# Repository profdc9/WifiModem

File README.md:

# WiFi Modem

This is a simple layout for connection a ESP12E to a serial port so that a serial to wireless gateway can be used.  It connects RTS/CTS for flow control (when supported) and has DB9 female/male and DB25 female/male connectors.  The particular gender of the connector can be mounted on the side of the board indicated by the silkscreening.  DB25 male is used to connect directly to an Apple Super Serial Card.  DB25 female is the standard connection of old-style dialup modems.  There are jumpers that swap TXD/RXD, RTS/CTS, and DTR/DSR to implement a built-in null modem changer.

There are several types of firmware that could be used on it.

https://github.com/jeelabs/esp-link

ESP Link is a firmware that enables remote access to a microcontroller or serial port through a web page or TCP port.

https://github.com/dhansel/WifiModem

https://github.com/jsalin/esp8266_modem

https://github.com/maccasoft/WifiModem/blob/master/WifiModem.ino

https://github.com/ssshake/vintage-computer-wifi-modem

https://github.com/stardot/esp8266_modem/wiki

https://github.com/RolandJuno/esp8266_modem    (implements CTS)

https://github.com/bozimmerman/Zimodem

A firmware image "zimodem.ino.nodemcu-3.4.bin" may be downloaded from:

http://subethasoftware.com/files/zimodem/

For using with ZiModem, use the following settings:

```
ATS47=5
OK
ATS49=15
OK
ATS51=13
OK
ATS53=12
OK
ATS55=14
OK
ATS57=4
OK
ATB9600
OK
AT&W
```
(default baud rate 9600 for example)

If you use the Zimodem firmware (current version 3.7.0 in that directory) that is in the "zimodem-firmware" directory, it is already compiled to point DTR/DSR/RI/RTS/CTS to the correct GPIO pins.  The default baud rate is 1200.  You can use esptool.py or the flash download tool to load it to the address 0x0000.

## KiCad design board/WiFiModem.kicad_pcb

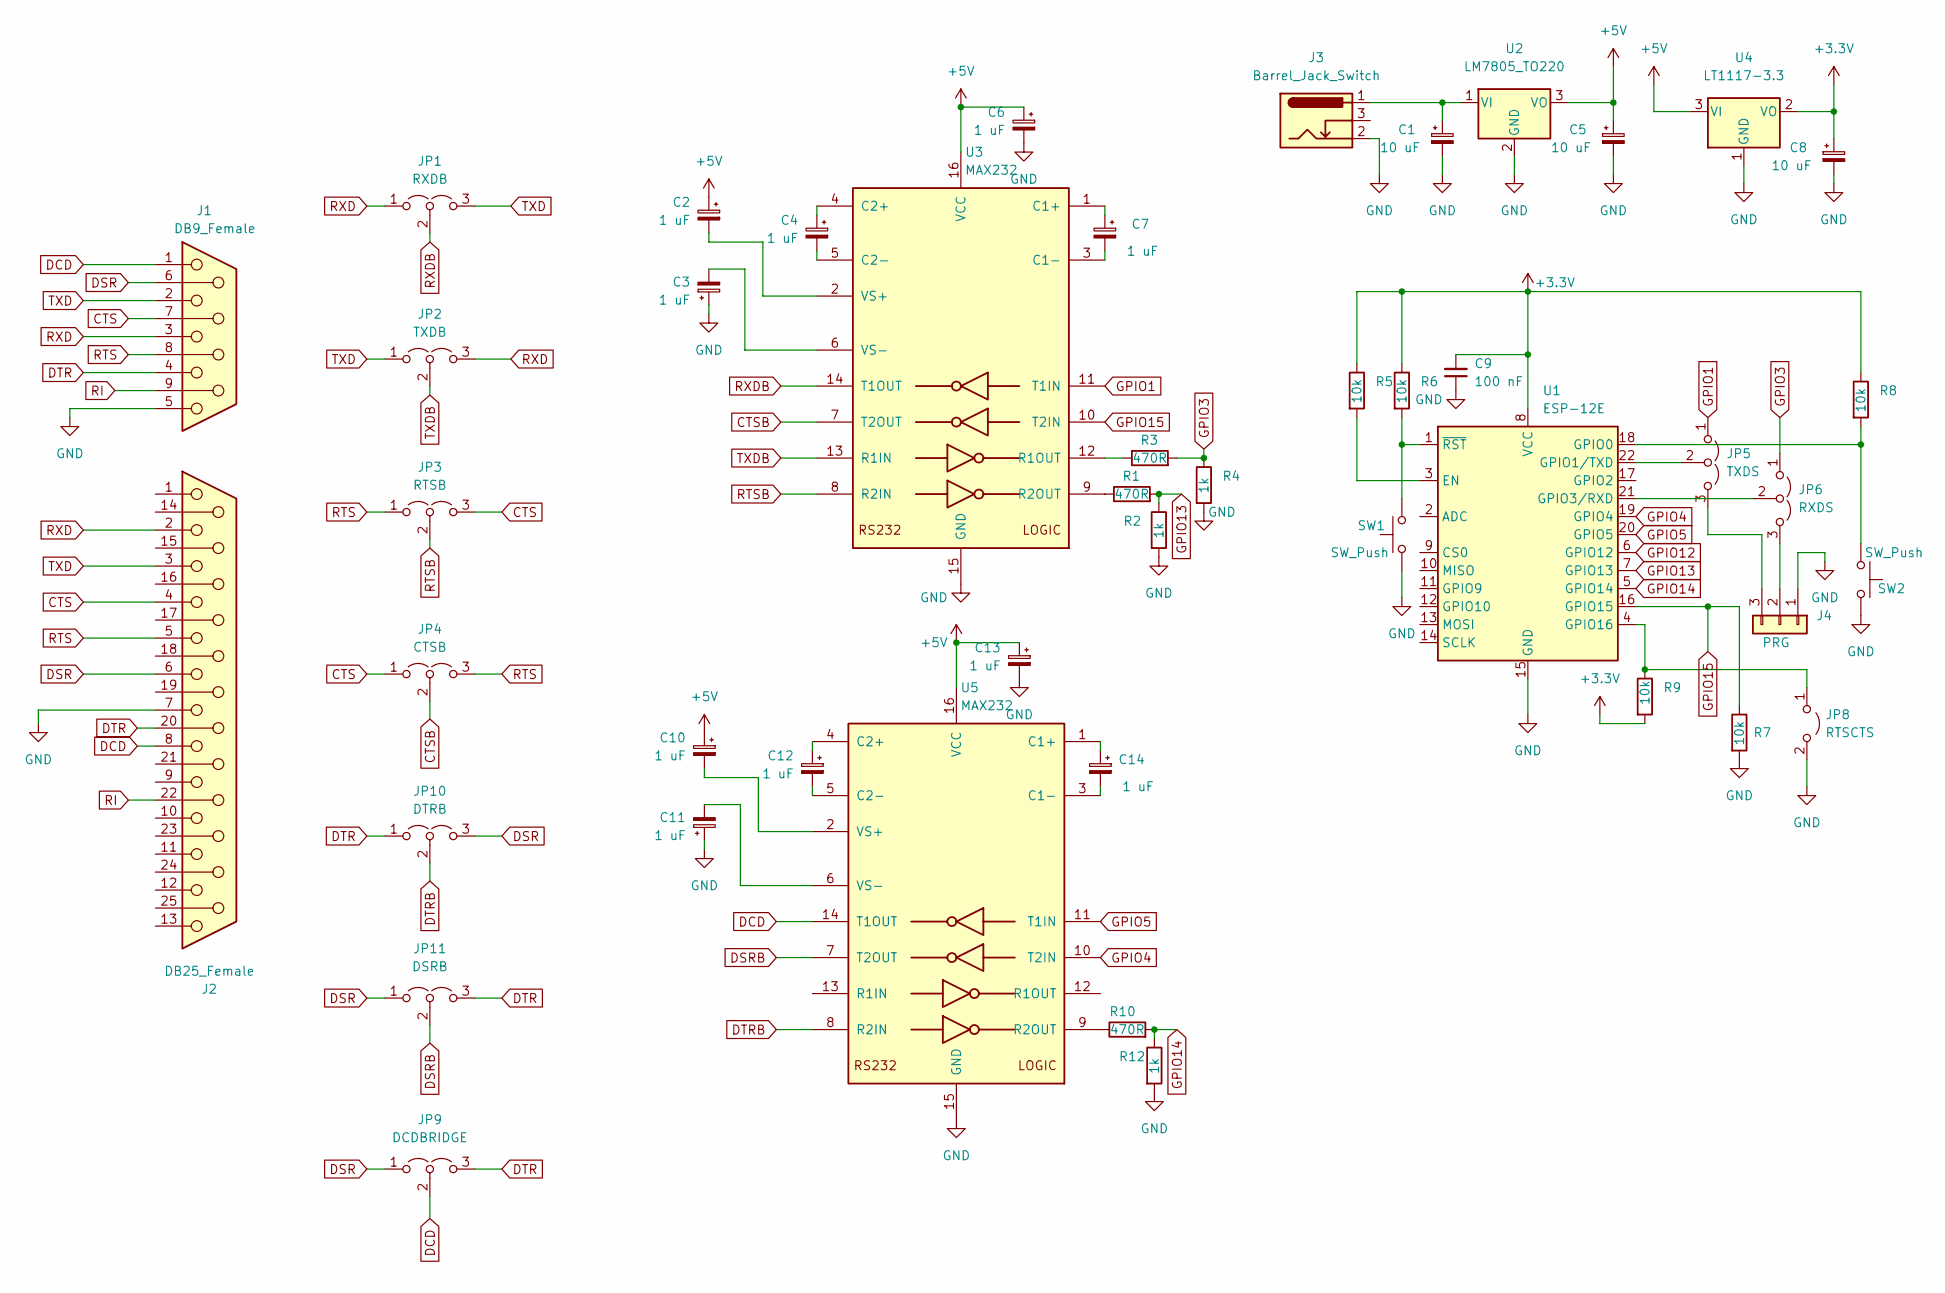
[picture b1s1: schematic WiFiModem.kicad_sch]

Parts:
C1, C5, C8: 10 uF; CP_Radial_D5.0mm_P2.00mm
C2, C3, C4, C6, C7, C10, C11, C12, C13, C14: 1 uF; CP_Radial_D5.0mm_P2.00mm
C9: 100 nF; C_Disc_D5.0mm_W2.5mm_P5.00mm
J1: DB9_Female; DSUB-9_Female_Horizontal_P2.77x2.84mm_EdgePinOffset4.94mm_H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
J2: DB25_Female; DSUB-25_Female_Horizontal_P2.77x2.84mm_EdgePinOffset7.70mm_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
J3: Barrel_Jack_Switch; BarrelJack_Horizontal
J4: PRG; PinHeader_1x03_P2.54mm_Vertical
JP1: RXDB; PinHeader_1x03_P2.54mm_Vertical
JP2: TXDB; PinHeader_1x03_P2.54mm_Vertical
JP3: RTSB; PinHeader_1x03_P2.54mm_Vertical
JP4: CTSB; PinHeader_1x03_P2.54mm_Vertical
JP5: TXDS; PinHeader_1x03_P2.54mm_Vertical
JP6: RXDS; PinHeader_1x03_P2.54mm_Vertical
JP8: RTSCTS; PinHeader_1x02_P2.54mm_Vertical
JP9: DCDBRIDGE; PinHeader_1x03_P2.54mm_Vertical
JP10: DTRB; PinHeader_1x03_P2.54mm_Vertical
JP11: DSRB; PinHeader_1x03_P2.54mm_Vertical
R1, R3, R10: 470R; R_Axial_DIN0207_L6.3mm_D2.5mm_P7.62mm_Horizontal
R2, R4, R12: 1k; R_Axial_DIN0207_L6.3mm_D2.5mm_P7.62mm_Horizontal
R5, R6, R7, R8, R9: 10k; R_Axial_DIN0207_L6.3mm_D2.5mm_P7.62mm_Horizontal
SW1, SW2: SW_Push; SW_PUSH_6mm
U1: ESP-12E
U2: LM7805_TO220; TO-220-3_Horizontal_TabDown
U3, U5: MAX232; DIP-16_W7.62mm_Socket
U4: LT1117-3.3; TO-220-3_Horizontal_TabDown

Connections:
+3V3: C8.1, C9.2, R5.1, R6.1, R8.1, R9.2, U1.8 (VCC), U4.2 (VO)
+5V: C2.1, C5.1, C6.1, C10.1, C13.1, U2.3 (VO), U3.16 (VCC), U4.3 (VI), U5.16 (VCC)
CTS: J1.7, J2.4, JP3.3 (B), JP4.1 (A)
CTSB: JP4.2 (C), U3.7 (T2OUT)
DCD: J1.1, J2.8, JP9.2 (C), U5.14 (T1OUT)
DSR: J1.6, J2.6, JP9.1 (A), JP10.3 (B), JP11.1 (A)
DSRB: JP11.2 (C), U5.7 (T2OUT)
DTR: J1.4, J2.20, JP9.3 (B), JP10.1 (A), JP11.3 (B)
DTRB: JP10.2 (C), U5.8 (R2IN)
GND: C1.2, C3.1, C5.2, C6.2, C8.2, C9.1, C11.1, C13.2, J1.5, J2.7, J3.2, J4.1, JP8.2 (B), R2.2, R4.2, R7.2, R12.2, SW1.1, SW2.2, U1.15 (GND), U2.2 (GND), U3.15 (GND), U4.1 (GND), U5.15 (GND)
GPIO1: JP5.1 (A), U3.11 (T1IN)
GPIO3: JP6.1 (A), R3.2, R4.1
GPIO4: U1.19 (GPIO4), U5.10 (T2IN)
GPIO5: U1.20 (GPIO5), U5.11 (T1IN)
GPIO12: U1.6 (GPIO12)
GPIO13: R1.2, R2.1, U1.7 (GPIO13)
GPIO14: R10.2, R12.1, U1.5 (GPIO14)
GPIO15: R7.1, U1.16 (GPIO15), U3.10 (T2IN)
unnamed: C1.1, J3.1, U2.1 (VI)
unnamed: C2.2, U3.2 (VS+)
unnamed: C3.2, U3.6 (VS-)
unnamed: C4.1, U3.4 (C2+)
unnamed: C4.2, U3.5 (C2-)
unnamed: C7.1, U3.1 (C1+)
unnamed: C7.2, U3.3 (C1-)
unnamed: C10.2, U5.2 (VS+)
unnamed: C11.2, U5.6 (VS-)
unnamed: C12.1, U5.4 (C2+)
unnamed: C12.2, U5.5 (C2-)
unnamed: C14.1, U5.1 (C1+)
unnamed: C14.2, U5.3 (C1-)
unnamed: J4.2, JP6.3 (B)
unnamed: J4.3, JP5.3 (B)
unnamed: JP5.2 (C), U1.22 (GPIO1/TXD)
unnamed: JP6.2 (C), U1.21 (GPIO3/RXD)
unnamed: JP8.1 (A), R9.1, U1.4 (GPIO16)
unnamed: R1.1, U3.9 (R2OUT)
unnamed: R3.1, U3.12 (R1OUT)
unnamed: R5.2, U1.3 (EN)
unnamed: R6.2, SW1.2, U1.1 (~RST)
unnamed: R8.2, SW2.1, U1.18 (GPIO0)
unnamed: R10.1, U5.9 (R2OUT)
RI: J1.9, J2.22
RTS: J1.8, J2.5, JP3.1 (A), JP4.3 (B)
RTSB: JP3.2 (C), U3.8 (R2IN)
RXD: J1.3, J2.2, JP1.1 (A), JP2.3 (B)
RXDB: JP1.2 (C), U3.14 (T1OUT)
TXD: J1.2, J2.3, JP1.3 (B), JP2.1 (A)
TXDB: JP2.2 (C), U3.13 (R1IN)

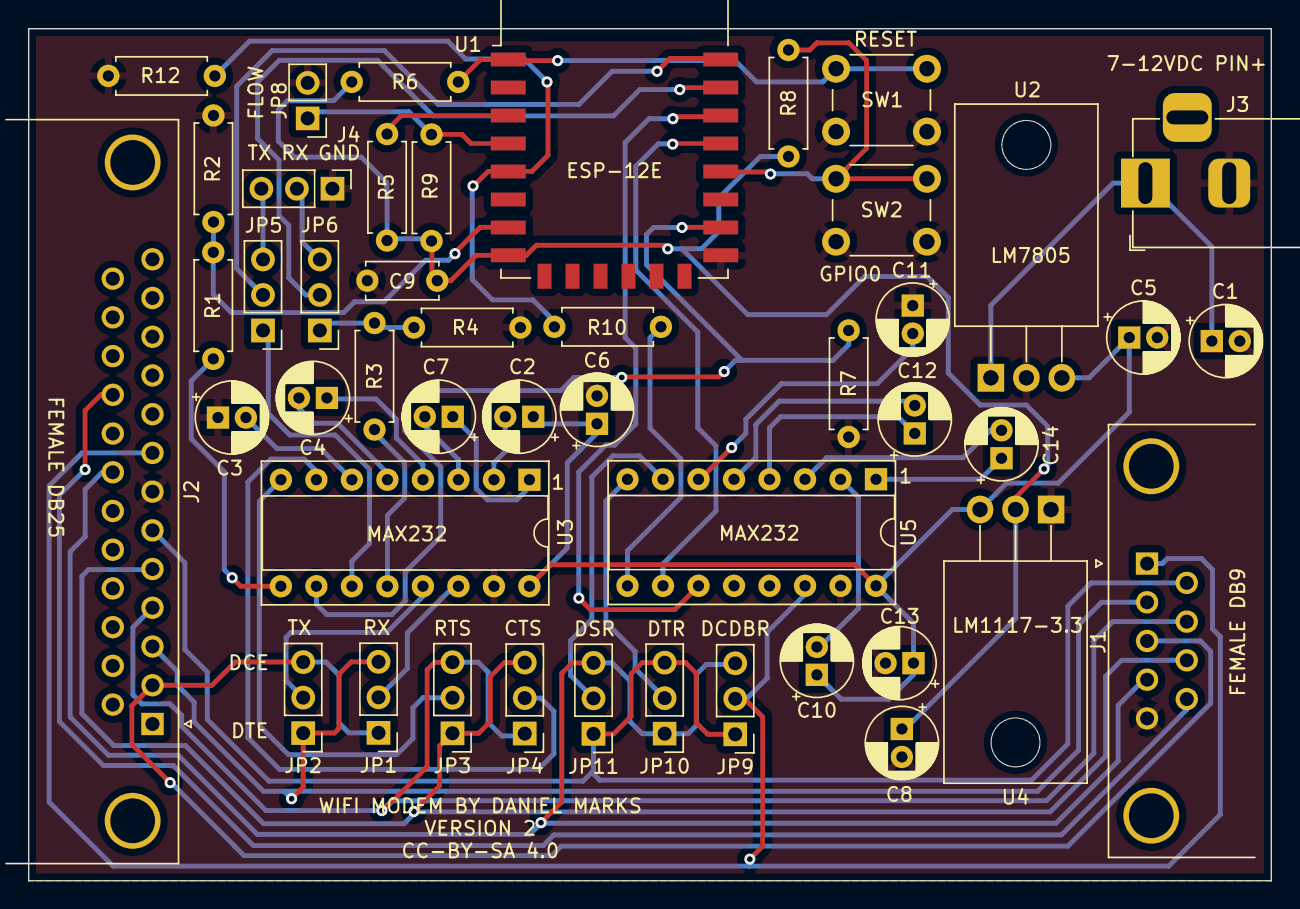
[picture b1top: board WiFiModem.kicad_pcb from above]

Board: 2 copper layers, 88.9 x 61.0 mm, 46 parts (0 on the bottom side), 48 nets.

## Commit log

2022-07-06 swap RTS and CTS
2022-07-06 Added flow control enable GPIO
2022-07-09 Added all of the other control signals
2022-07-10 Changed from DB25 male to DB25 female
2022-07-11 Added silkscreening to indicate male/female sides
2022-07-24 Fixed GPIO15 booting issue, changed DCD/DSR/DTR jumper
2022-07-25 Added zimodem firmware
2022-07-25 Recompiled with correct library
2022-07-31 Fixed DCD and DB25 pinouts
2022-08-01 Moved around some traces
2022-08-22 Added picture of completed boarD

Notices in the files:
board/WiFiModem.kicad_pcb:
CC-BY-SA 4.0
